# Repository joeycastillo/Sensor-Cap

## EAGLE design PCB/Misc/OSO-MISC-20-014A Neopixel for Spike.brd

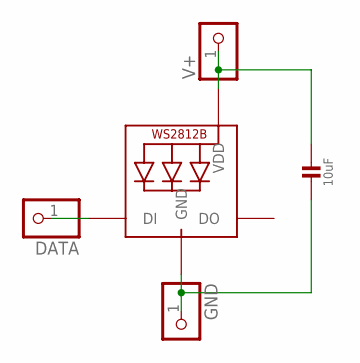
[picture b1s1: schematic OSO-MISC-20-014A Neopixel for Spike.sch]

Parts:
C1: 10uF; 0805-NO
DATA: PINHD-1X1; 1X01
GND: PINHD-1X1; 1X01
LED1: WS2812B3535; LED3535
V+: PINHD-1X1; 1X01

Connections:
unnamed: DATA.1, LED1.1 (DI)
unnamed: C1.1, LED1.2 (VDD), V+.1
unnamed: C1.2, GND.1, LED1.4 (GND)

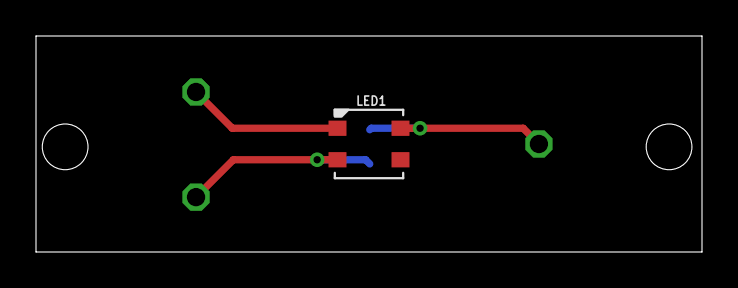
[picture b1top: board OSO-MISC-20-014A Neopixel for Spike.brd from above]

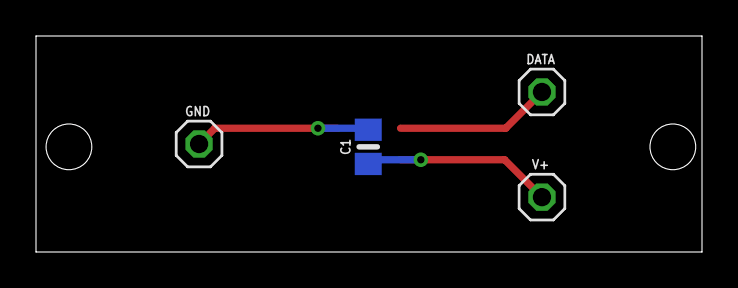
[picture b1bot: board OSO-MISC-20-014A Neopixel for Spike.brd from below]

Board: 2 copper layers, 37.0 x 12.0 mm, 5 parts (4 on the bottom side), 3 nets.

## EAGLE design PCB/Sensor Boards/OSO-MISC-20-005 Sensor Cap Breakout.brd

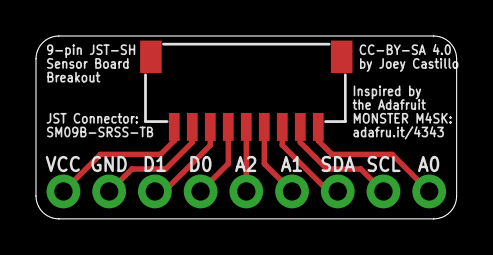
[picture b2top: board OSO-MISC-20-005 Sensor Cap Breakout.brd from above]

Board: 2 copper layers, 23.4 x 10.2 mm, 3 parts (1 on the bottom side), 9 nets.

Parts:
J1: 1X09_NO_SILK
JP1: JST_SH9
U$1: OSO_WORDMARK_ONELINE_725MIL_1000DPI

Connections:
+3V3: J1.9, JP1.9
A0: J1.1, JP1.1
A1: J1.4, JP1.4
A2: J1.5, JP1.5
D0/A3: J1.6, JP1.6
D1/A4: J1.7, JP1.7
GND: J1.8, JP1.8
SCL: J1.2, JP1.2
SDA: J1.3, JP1.3

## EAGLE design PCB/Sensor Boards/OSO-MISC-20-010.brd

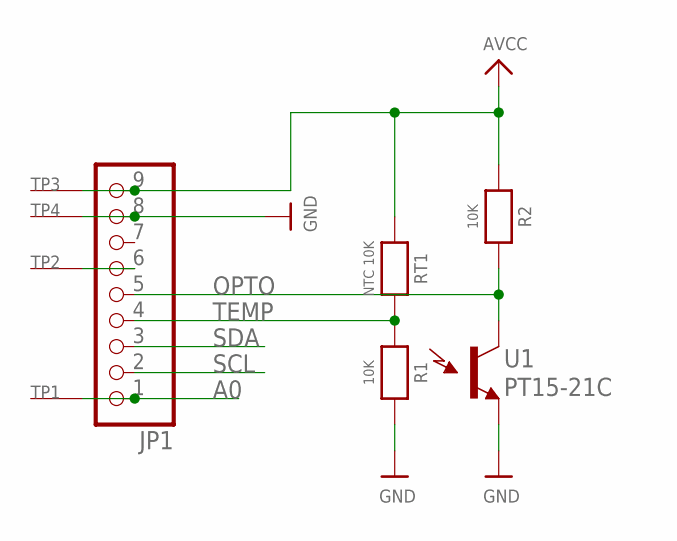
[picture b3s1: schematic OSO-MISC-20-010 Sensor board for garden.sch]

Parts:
JP1: HEADER-1X9_JSTSH; JST_SH9
R1, R2: 10K; 0805-NO
RT1: NTC 10K; 0805-NO
TP1, TP2, TP3, TP4: SEWTAP0.5IN; SEWINGTAP_0.5
U1: PT15-21C; LED-1206

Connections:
A0: JP1.1, TP1.TAP
AVCC: JP1.9, R2.1, RT1.1, TP3.TAP
GND: JP1.8, R1.2, TP4.TAP, U1.C (E1)
unnamed: JP1.6, TP2.TAP
OPTO: JP1.5, R2.2, U1.A (C1)
SCL: JP1.2
SDA: JP1.3
TEMP: JP1.4, R1.1, RT1.2

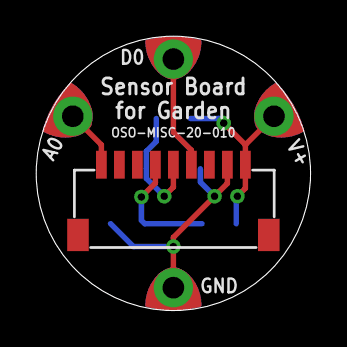
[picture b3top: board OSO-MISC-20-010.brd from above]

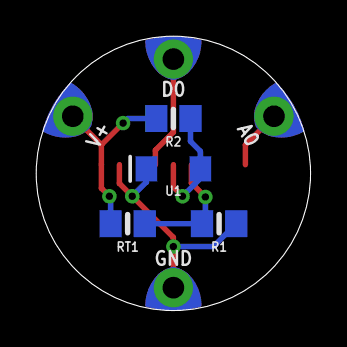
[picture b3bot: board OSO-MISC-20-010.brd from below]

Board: 2 copper layers, 15.2 x 15.2 mm, 9 parts (4 on the bottom side), 6 nets.

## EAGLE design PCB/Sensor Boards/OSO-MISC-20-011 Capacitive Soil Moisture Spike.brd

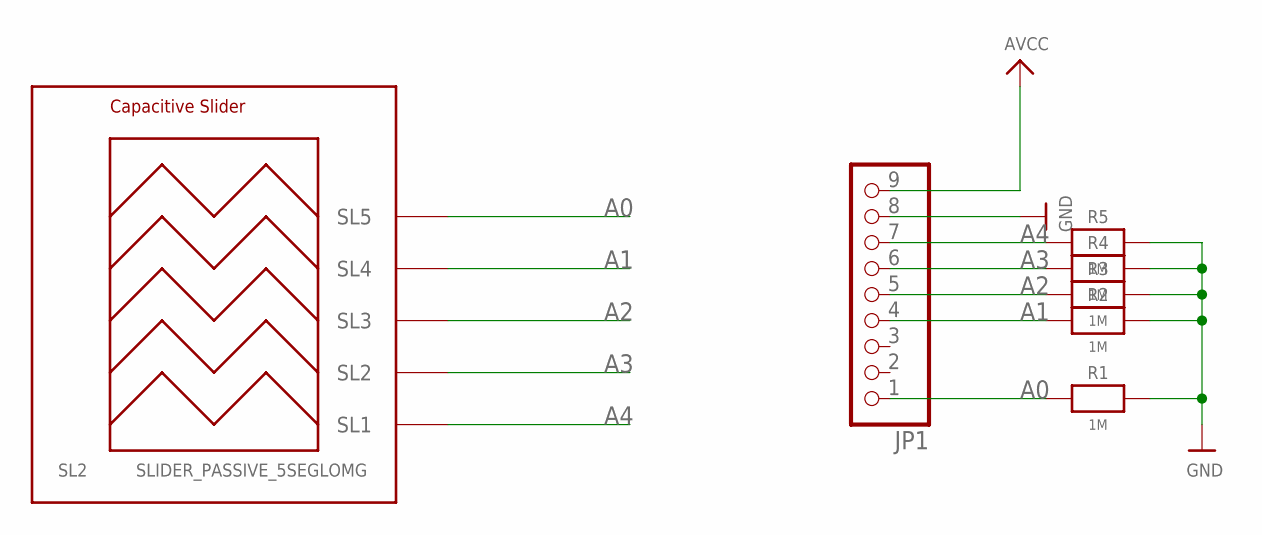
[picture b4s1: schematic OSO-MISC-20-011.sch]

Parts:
JP1: HEADER-1X9_JSTSH; JST_SH9
R1, R2, R3, R4, R5: 1M; 0603-NO
SL2: SLIDER_PASSIVE_5SEGLOMG; SLIDER_PASSIVE_5SEG_12MM_LOMG

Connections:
A0: JP1.1, R1.1, SL2.SL5
A1: JP1.4, R2.1, SL2.SL4
A2: JP1.5, R3.1, SL2.SL3
A3: JP1.6, R4.1, SL2.SL2
A4: JP1.7, R5.1, SL2.SL1
AVCC: JP1.9
GND: JP1.8, R1.2, R2.2, R3.2, R4.2, R5.2

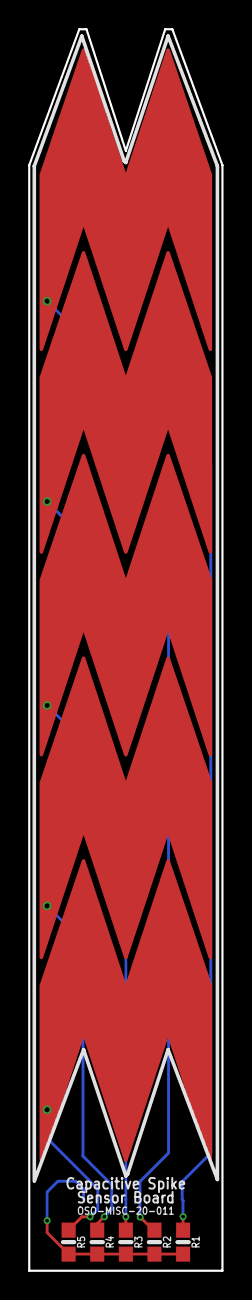
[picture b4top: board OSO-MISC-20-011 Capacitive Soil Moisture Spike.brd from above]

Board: 2 copper layers, 13.7 x 88.1 mm, 7 parts (1 on the bottom side), 6 nets.

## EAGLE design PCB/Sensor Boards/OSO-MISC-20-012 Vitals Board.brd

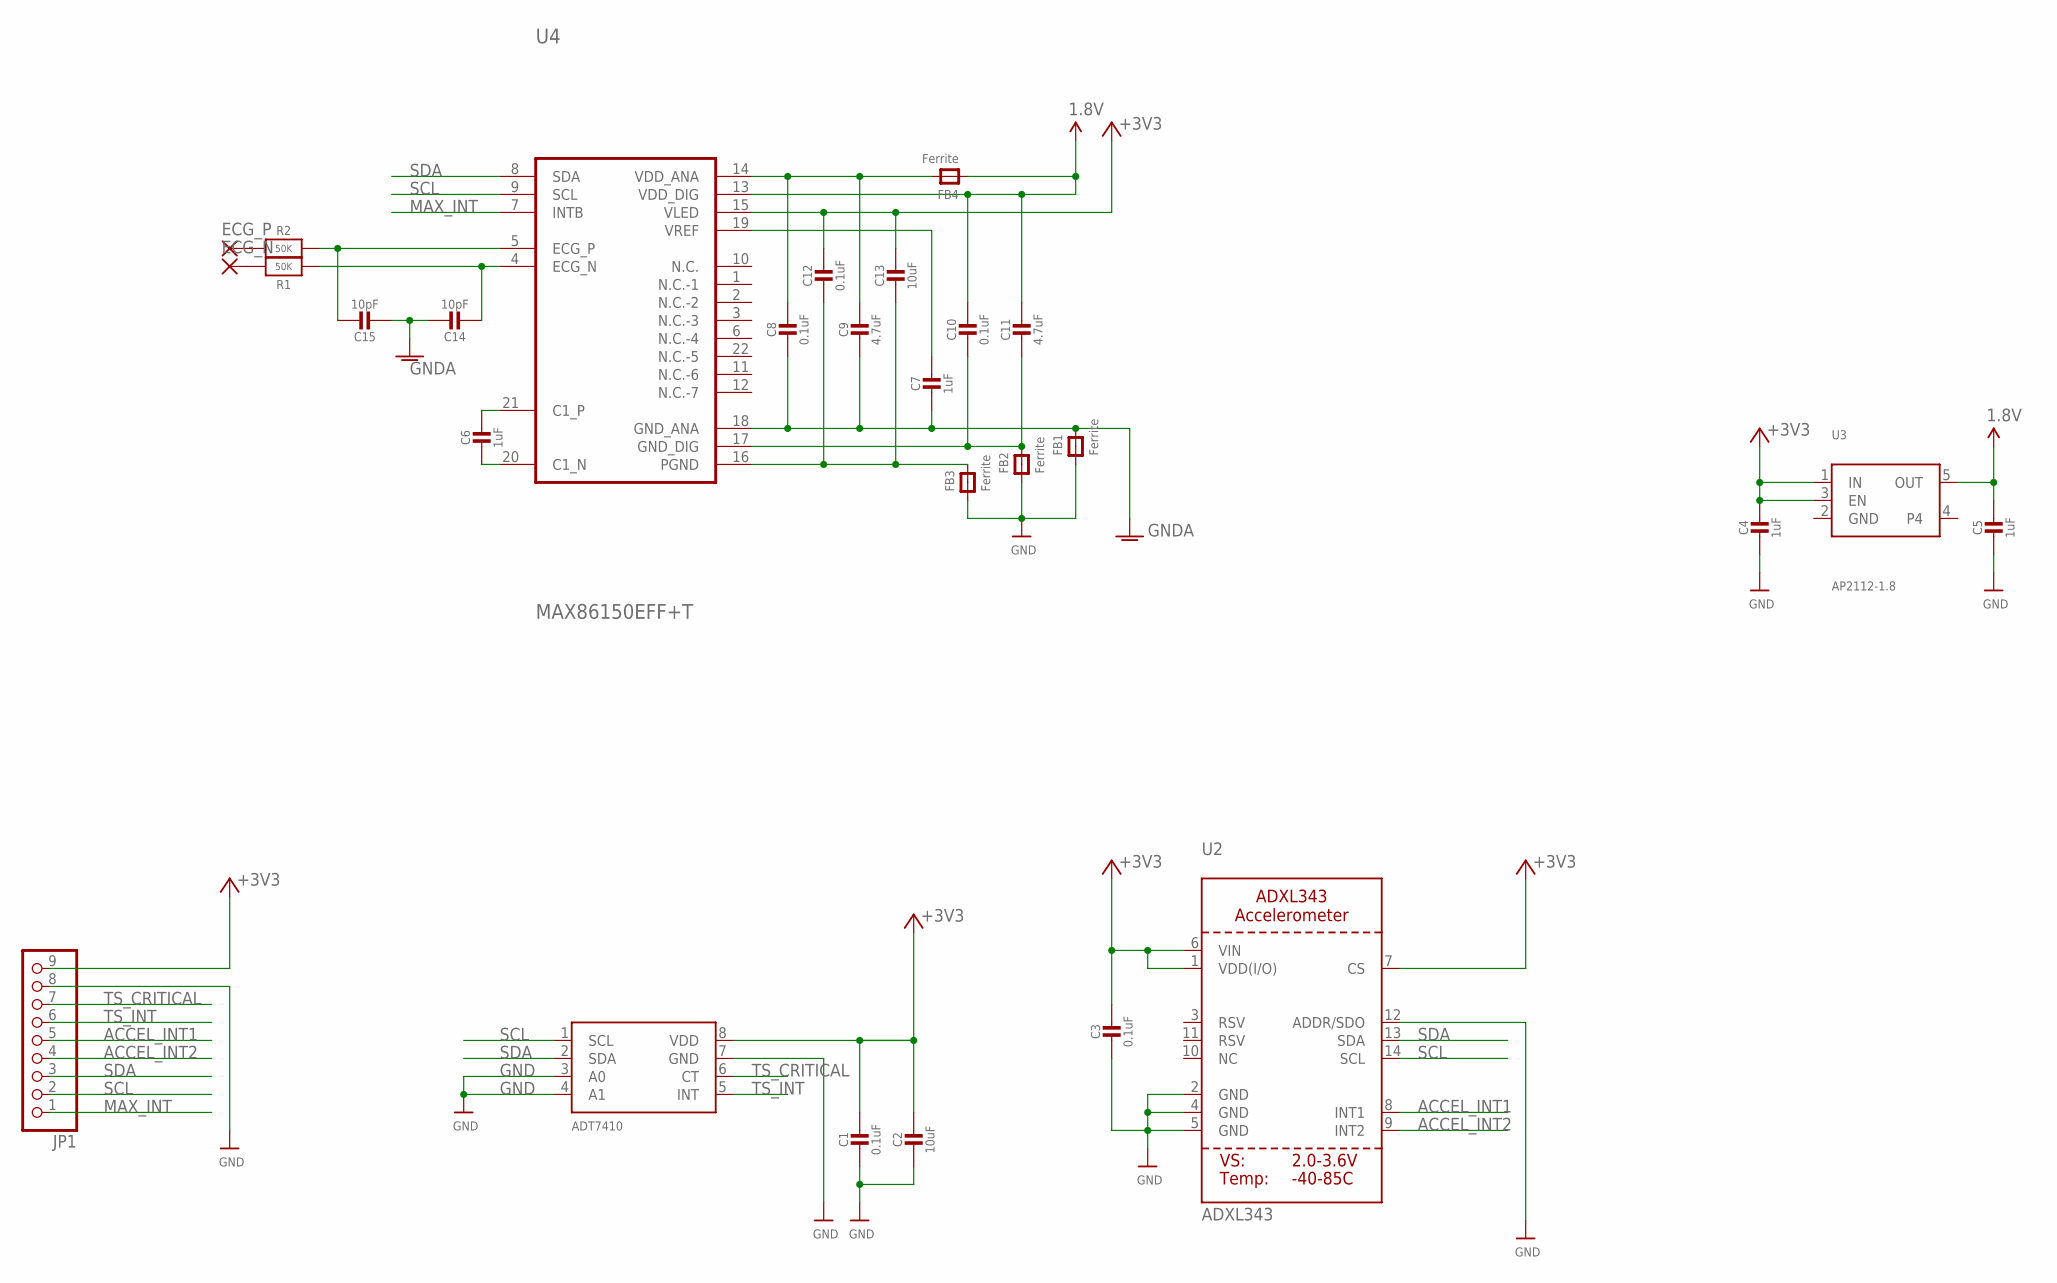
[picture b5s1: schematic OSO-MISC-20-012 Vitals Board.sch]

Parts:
C1, C3, C8, C10, C12: 0.1uF; 0603-NO
C2, C13: 10uF; 0805-NO
C4, C5, C7: 1uF; 0603-NO
C6: 1uF; 0805-NO
C9, C11: 4.7uF; 0805-NO
C14, C15: 10pF; 0805-NO
ECG_N: SMD5; SMD2,54-5,08
ECG_P: SMD5; SMD2,54-5,08
FB1, FB2, FB3, FB4: Ferrite; _0805MP
JP1: HEADER-1X9_JSTSH; JST_SH9
R1, R2: 50K; 0603-NO
U1: ADT7410; SOIC8_150MIL
U2: ADXL343; LGA14
U3: AP2112-1.8; SOT23-5
U4: MAX86150EFF+T; XDCR_MAX86150EFF+

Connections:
1.8V: C5.1, C10.1, C11.1, FB4.1, U3.5 (OUT), U4.13 (VDD_DIG)
1V8_ANA: C8.1, C9.1, FB4.2, U4.14 (VDD_ANA)
+3V3: C1.1, C2.1, C3.1, C4.1, C12.1, C13.1, JP1.9, U1.8 (VDD), U2.1 (VDD(I/O)), U2.6 (VIN), U2.7 (CS), U3.1 (IN), U3.3 (EN), U4.15 (VLED)
ACCEL_INT1: JP1.5, U2.8 (INT1)
ACCEL_INT2: JP1.4, U2.9 (INT2)
GND: C1.2, C2.2, C3.2, C4.2, C5.2, FB1.1, FB2.1, FB3.1, JP1.8, U1.3 (A0), U1.4 (A1), U1.7 (GND), U2.2 (GND), U2.4 (GND), U2.5 (GND), U2.12 (ADDR/SDO), U3.2 (GND)
GNDA: C7.2, C8.2, C9.2, C14.1, C15.2, FB1.2, U4.18 (GND_ANA)
GND_DIG: C10.2, C11.2, FB2.2, U4.17 (GND_DIG)
MAX_INT: JP1.1, U4.7 (INTB)
unnamed: ECG_P.1, R2.1
unnamed: ECG_N.1, R1.1
unnamed: C15.1, R2.2, U4.5 (ECG_P)
unnamed: C6.1, U4.21 (C1_P)
unnamed: C6.2, U4.20 (C1_N)
unnamed: C14.2, R1.2, U4.4 (ECG_N)
PGND: C12.2, C13.2, FB3.2, U4.16 (PGND)
SCL: JP1.2, U1.1 (SCL), U2.14 (SCL), U4.9 (SCL)
SDA: JP1.3, U1.2 (SDA), U2.13 (SDA), U4.8 (SDA)
TS_CRITICAL: JP1.7, U1.6 (CT)
TS_INT: JP1.6, U1.5 (INT)
VREF: C7.1, U4.19 (VREF)

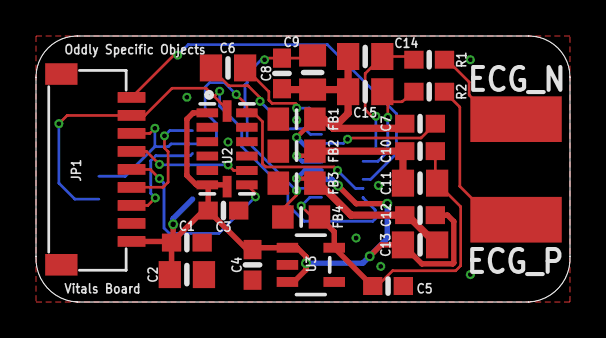
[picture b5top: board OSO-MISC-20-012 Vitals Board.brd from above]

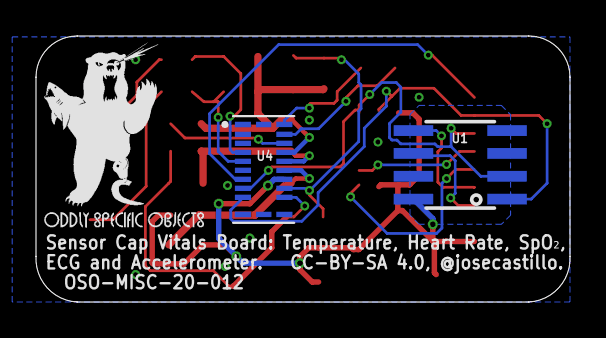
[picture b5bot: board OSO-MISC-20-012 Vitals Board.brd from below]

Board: 2 copper layers, 29.7 x 14.8 mm, 30 parts (4 on the bottom side), 21 nets.

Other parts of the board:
U$3: OSO_BEAR_250X360MIL_1000DPI
U$7: OSO_WORDMARK_ONELINE_350MIL_1000DPI

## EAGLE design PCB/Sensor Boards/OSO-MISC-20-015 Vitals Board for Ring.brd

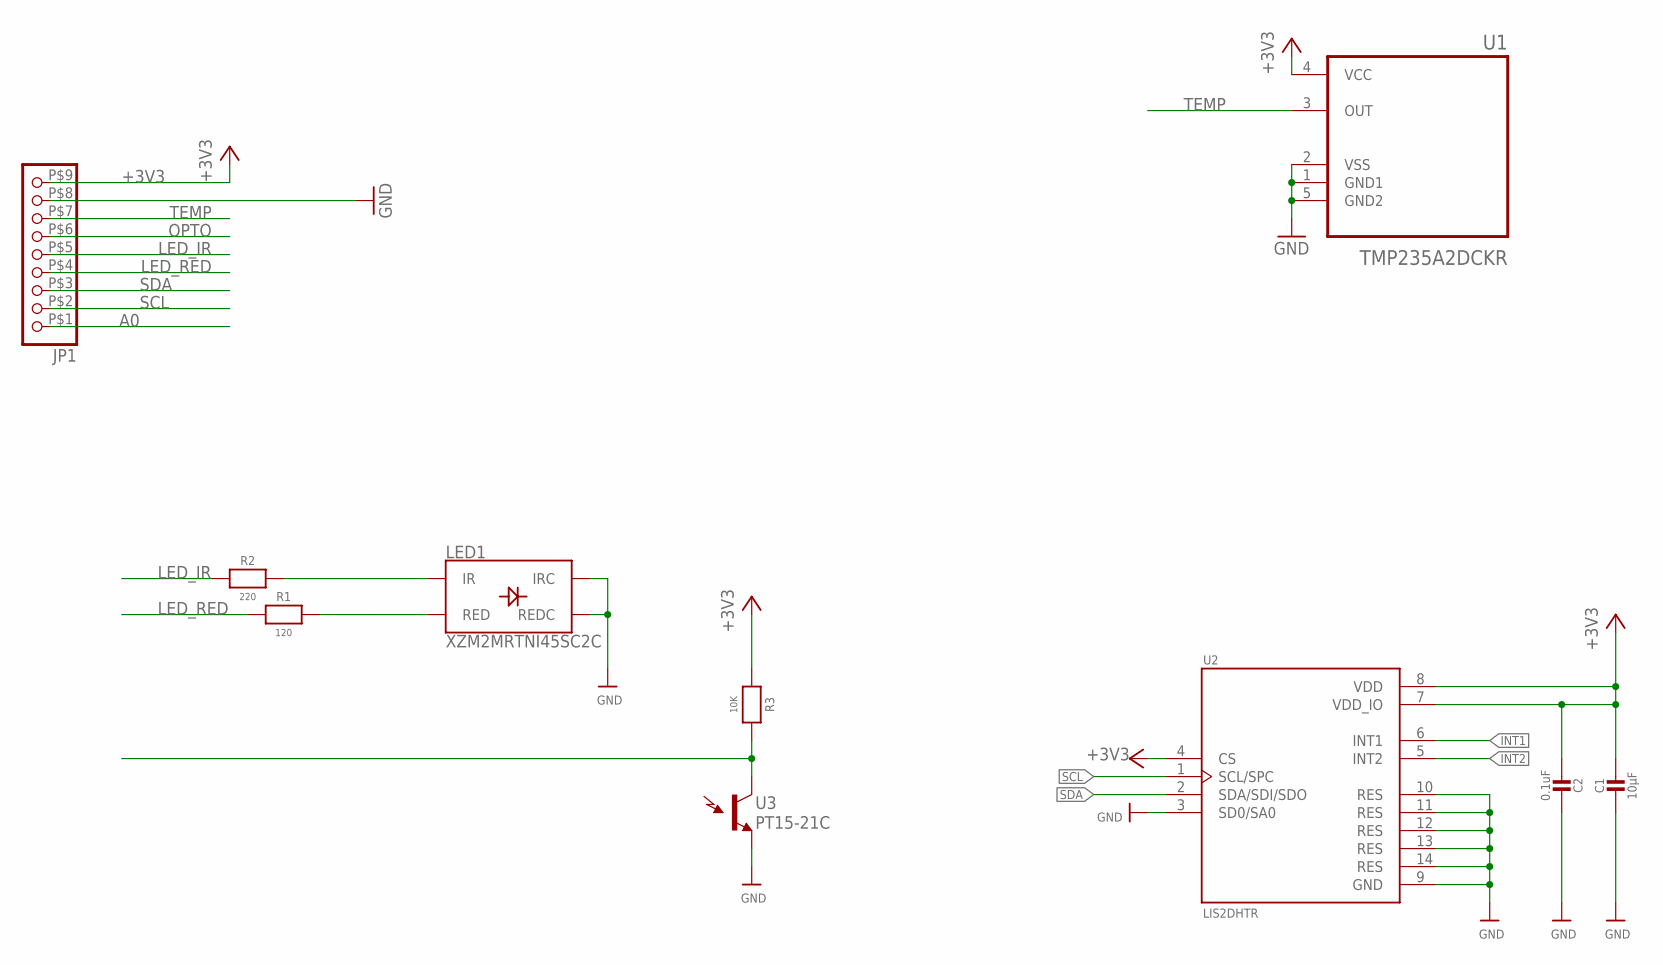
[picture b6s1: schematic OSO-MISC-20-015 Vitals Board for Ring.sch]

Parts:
C1: 10µF; 0603-NO
C2: 0.1uF; 0603-NO
JP1: HEADER-1X9BOARD_TO_FLEX; 9PIN_SMT_CONNECTOR
LED1: XZM2MRTNI45SC2C; PLCC4SMDLED
R1: 120; 0603-NO
R2: 220; 0603-NO
R3: 10K; 0603-NO
U1: TMP235A2DCKR; SOT65P210X110-5N
U2: LIS2DHTR; PQFN35P200X200X100-14N
U3: PT15-21C; LED-1206

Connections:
+3V3: C1.1, C2.2, JP1.P$9 (9), R3.1, U1.4 (VCC), U2.4 (CS), U2.7 (VDD_IO), U2.8 (VDD)
A0: JP1.P$1 (1)
GND: C1.2, C2.1, JP1.P$8 (8), LED1.1 (REDC), LED1.3 (IRC), U1.1 (GND1), U1.2 (VSS), U1.5 (GND2), U2.3 (SD0/SA0), U2.9 (GND), U2.10 (RES), U2.11 (RES), U2.12 (RES), U2.13 (RES), U2.14 (RES), U3.C (E1)
INT1: U2.6 (INT1)
INT2: U2.5 (INT2)
IR_LIM: LED1.4 (IR), R2.2
LED_IR: JP1.P$5 (5), R2.1
LED_RED: JP1.P$4 (4), R1.1
OPTO: JP1.P$6 (6), R3.2, U3.A (C1)
RED_LIM: LED1.2 (RED), R1.2
SCL: JP1.P$2 (2), U2.1 (SCL/SPC)
SDA: JP1.P$3 (3), U2.2 (SDA/SDI/SDO)
TEMP: JP1.P$7 (7), U1.3 (OUT)

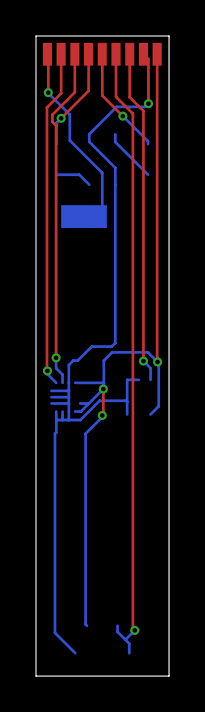
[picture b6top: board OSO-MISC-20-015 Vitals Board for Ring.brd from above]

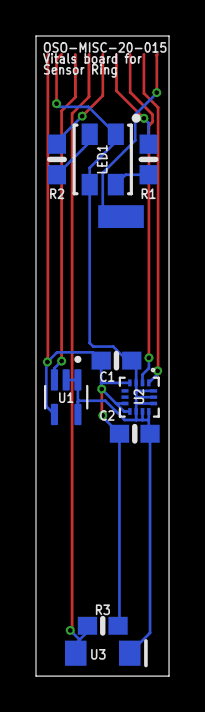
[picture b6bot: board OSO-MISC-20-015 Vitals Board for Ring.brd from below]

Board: 2 copper layers, 7.4 x 35.6 mm, 10 parts (9 on the bottom side), 10 nets.

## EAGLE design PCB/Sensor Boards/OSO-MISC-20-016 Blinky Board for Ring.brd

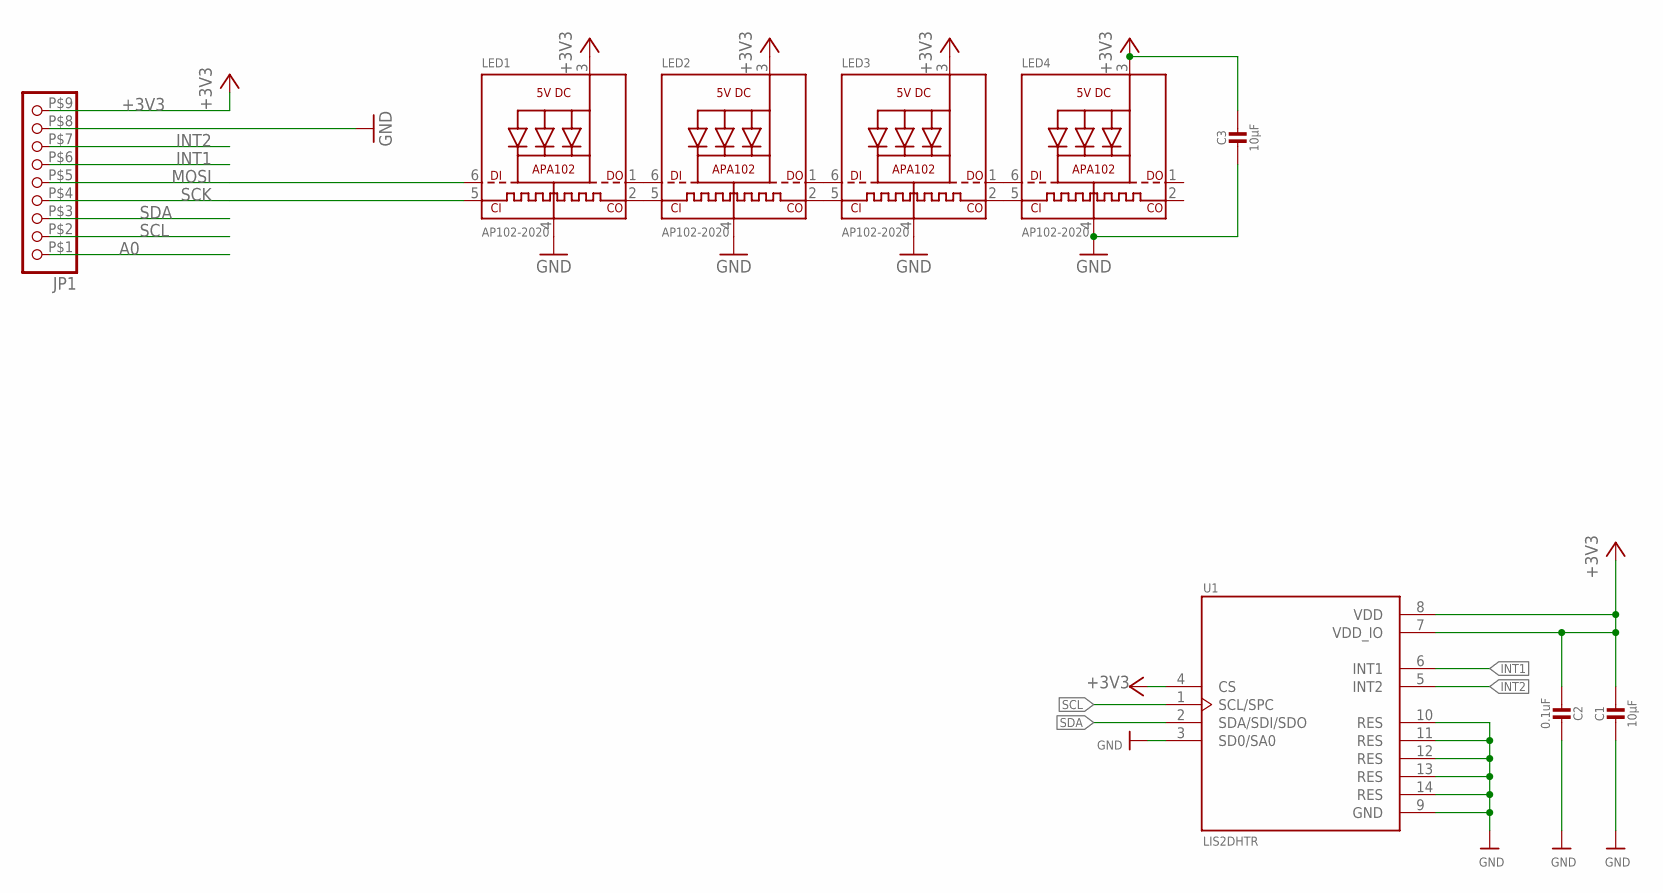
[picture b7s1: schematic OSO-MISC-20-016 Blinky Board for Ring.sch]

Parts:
C1, C3: 10µF; 0805-NO
C2: 0.1uF; 0805-NO
JP1: HEADER-1X9BOARD_TO_FLEX; 9PIN_SMT_CONNECTOR
LED1, LED2, LED3, LED4: AP102-2020; APA102_2020
U1: LIS2DHTR; PQFN35P200X200X100-14N

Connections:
+3V3: C1.1, C2.2, C3.1, JP1.P$9 (9), LED1.3 (VDD), LED2.3 (VDD), LED3.3 (VDD), LED4.3 (VDD), U1.4 (CS), U1.7 (VDD_IO), U1.8 (VDD)
A0: JP1.P$1 (1)
GND: C1.2, C2.1, C3.2, JP1.P$8 (8), LED1.4 (GND), LED2.4 (GND), LED3.4 (GND), LED4.4 (GND), U1.3 (SD0/SA0), U1.9 (GND), U1.10 (RES), U1.11 (RES), U1.12 (RES), U1.13 (RES), U1.14 (RES)
INT1: JP1.P$6 (6), U1.6 (INT1)
INT2: JP1.P$7 (7), U1.5 (INT2)
MOSI: JP1.P$5 (5), LED1.6 (DI)
unnamed: LED1.1 (DO), LED2.6 (DI)
unnamed: LED1.2 (CKO), LED2.5 (CKI)
unnamed: LED2.1 (DO), LED3.6 (DI)
unnamed: LED2.2 (CKO), LED3.5 (CKI)
unnamed: LED3.1 (DO), LED4.6 (DI)
unnamed: LED3.2 (CKO), LED4.5 (CKI)
SCK: JP1.P$4 (4), LED1.5 (CKI)
SCL: JP1.P$2 (2), U1.1 (SCL/SPC)
SDA: JP1.P$3 (3), U1.2 (SDA/SDI/SDO)

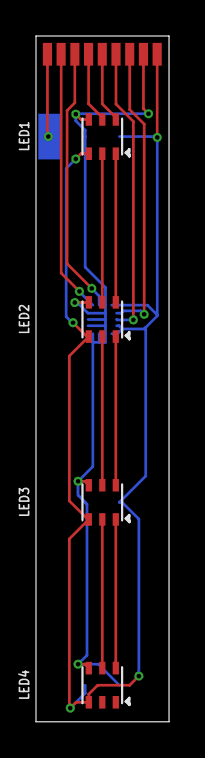
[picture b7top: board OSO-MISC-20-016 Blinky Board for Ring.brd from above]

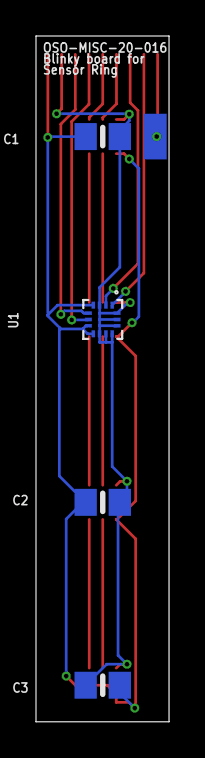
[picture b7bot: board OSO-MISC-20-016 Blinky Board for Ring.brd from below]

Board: 2 copper layers, 7.4 x 38.1 mm, 9 parts (4 on the bottom side), 14 nets.

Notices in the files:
PCB/Sensor Boards/OSO-MISC-20-005 Sensor Cap Breakout.brd:
CC-BY-SA 4.0
PCB/Sensor Boards/OSO-MISC-20-012 Vitals Board.brd:
Sensor Cap Vitals Board: Temperature, Heart Rate, SpO₂,
ECG and Accelerometer. CC-BY-SA 4.0, @josecastillo.
parts and their libraries:
microbuilder: This work is placed in the public domain, and may be freely used for commercial and non-commercial work with the following conditions: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
SparkFun-Connectors: Licensing: Creative Commons ShareAlike 4.0 International - https://creativecommons.org/licenses/by-sa/4.0
